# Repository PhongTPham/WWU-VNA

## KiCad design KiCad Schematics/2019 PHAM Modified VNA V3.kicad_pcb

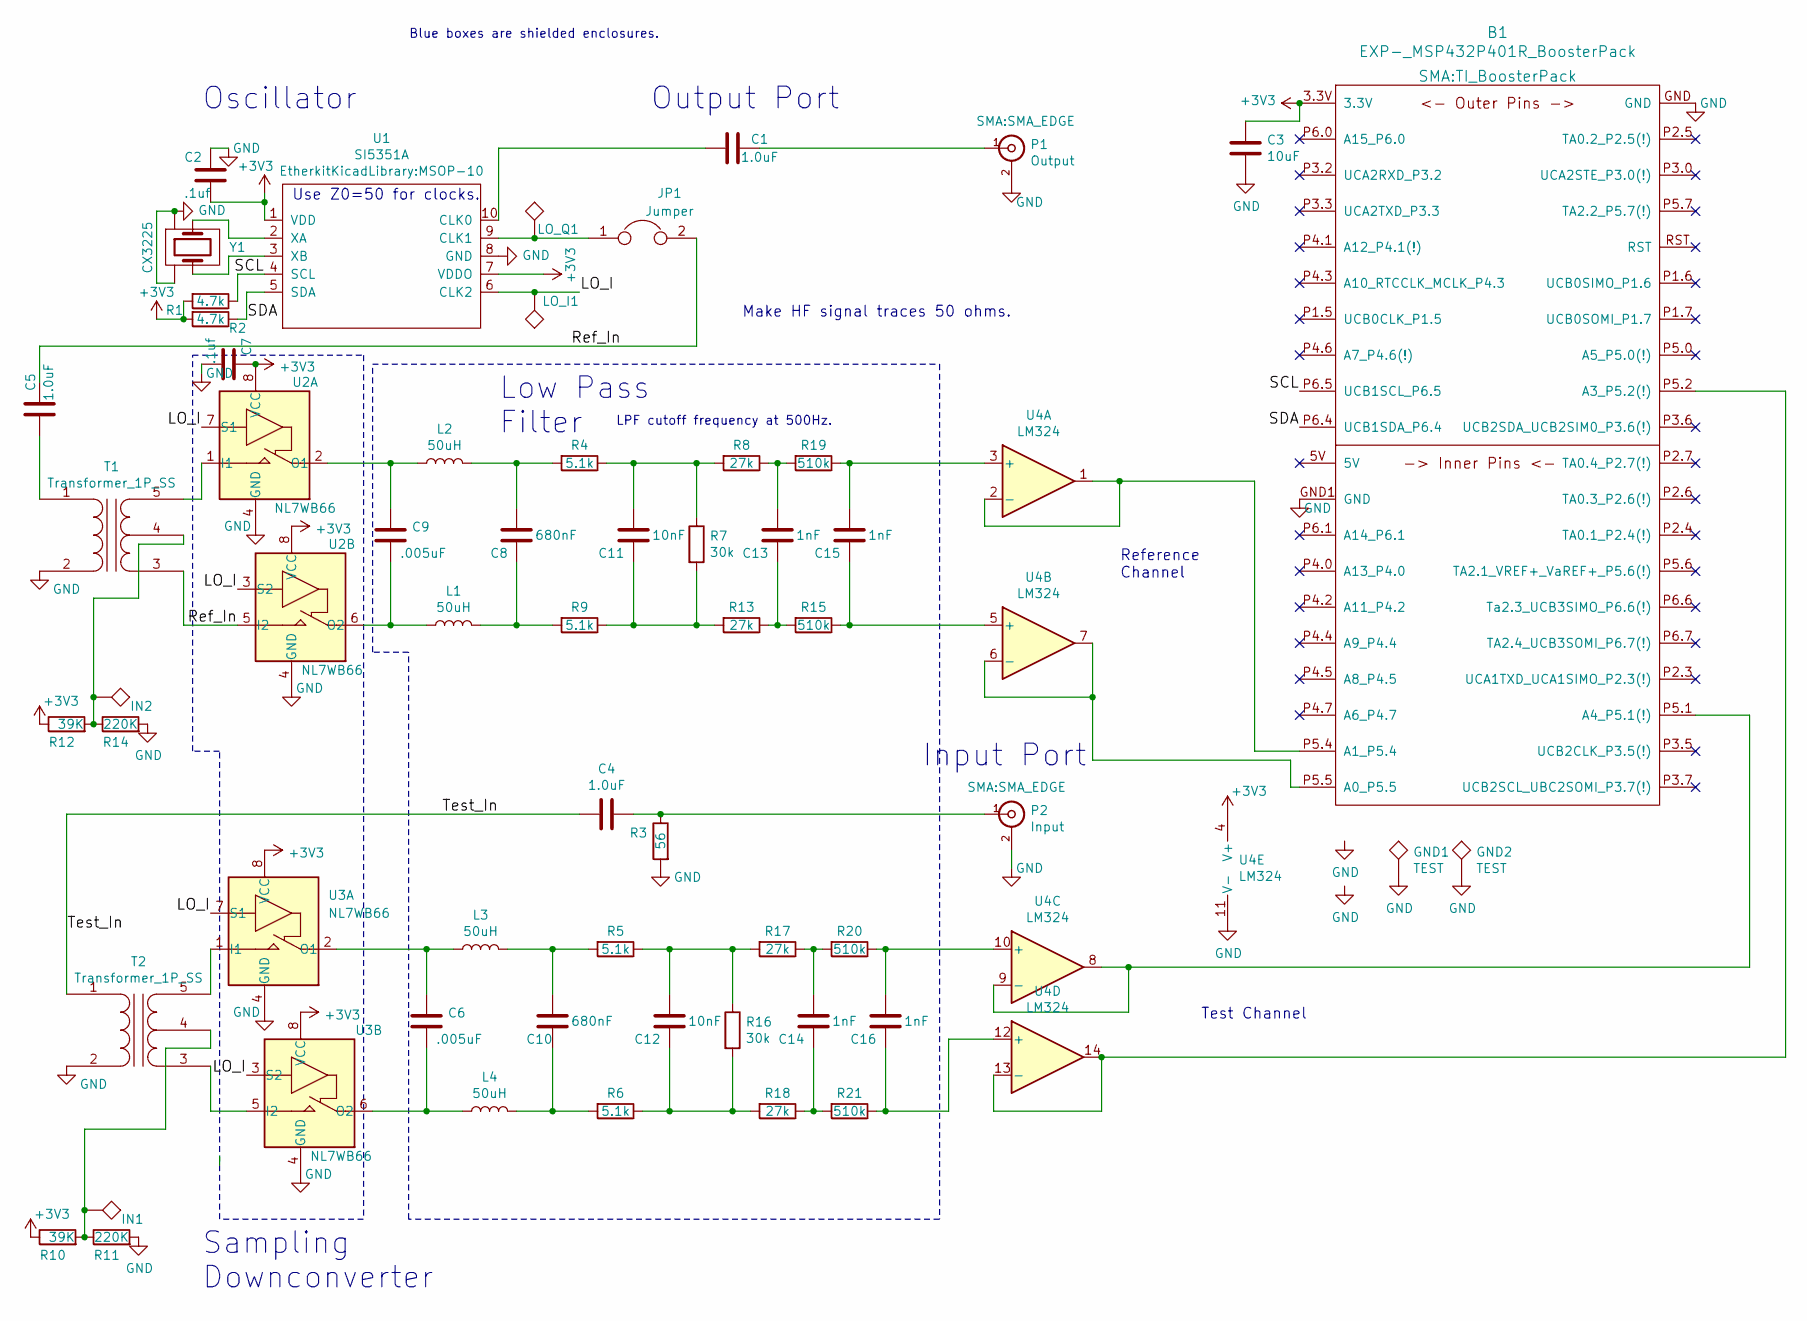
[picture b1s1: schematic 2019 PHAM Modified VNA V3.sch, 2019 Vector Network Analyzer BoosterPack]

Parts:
B1: EXP-_MSP432P401R_BoosterPack; TI_BoosterPack
C1, C4, C5: 1.0uF; C_0805
C2, C7: .1uf; C_0805
C3: 10uF; C_0805
C6, C9: .005uF; C_0805
C8, C10: 680nF; C_0805
C11, C12: 10nF; C_0805
C13, C14, C15, C16: 1nF; C_0805
GND1, GND2: TEST; TestPoint_Keystone_5000-5004_Miniature
IN1, IN2: IN; TestPoint_Keystone_5000-5004_Miniature
JP1: Jumper; SolderJumper-2_P1.3mm_Bridged2Bar_Pad1.0x1.5mm
L1, L2, L3, L4: 50uH; L_0805_2012Metric; Part Taiyo Yuden LB2012T101K
LO_I1: LO_I; TestPoint_Keystone_5000-5004_Miniature
LO_Q1: LO_Q; TestPoint_Keystone_5000-5004_Miniature
P1: Output; SMA_EDGE
P2: Input; SMA_EDGE
R1, R2: 4.7k; R_0805
R3: 56; R_0805
R4, R5, R6, R9: 5.1k; R_0805
R7, R16: 30k; R_0805
R8, R13, R17, R18: 27k; R_0805
R10, R12: 39K; R_0805
R11, R14: 220K; R_0805
R15, R19, R20, R21: 510k; R_0805
T1, T2: Transformer_1P_SS; Pulse_P0926NL
U1: SI5351A; MSOP-10
U2, U3: NL7WB66; VFSOP-8
U4: LM324; SOIC-14_3.9x8.7mm_P1.27mm
Y1: CX3225

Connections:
+3V3: B1.3.3V, C2.2, C3.1, C7.1, R1.2, R2.2, R10.1, R12.1, U1.1 (VDD), U1.7 (VDDO), U2.8 (VCC), U3.8 (VCC), U4.4 (V+)
/LO_I: LO_I1.1, U1.6 (CLK2), U2.3 (S2), U2.7 (S1), U3.3 (S2), U3.7 (S1)
/Ref_In: C5.1, JP1.2, T1.3 (SA), U2.5 (I2)
/SCL: B1.P6.5 (UCB1SCL_P6.5), R1.1, U1.4 (SCL)
/SDA: B1.P6.4 (UCB1SDA_P6.4), R2.1, U1.5 (SDA)
/Test_In: C4.1, T2.1 (AA)
GND: B1.GND, B1.GND1 (GND), C2.1, C3.2, C7.2, GND1.1, GND2.1, P1.2 (Ext), P2.2 (Ext), R3.2, R11.2, R14.2, T1.2 (AB), T2.2 (AB), U1.8 (GND), U2.4 (GND), U3.4 (GND), U4.11 (V-), Y1.2 (GND), Y1.4 (GND)
unnamed: B1.P5.1 (A4_P5.1(!)), U4.8, U4.9 (-)
unnamed: B1.P5.2 (A3_P5.2(!)), U4.13 (-), U4.14
unnamed: B1.P5.4 (A1_P5.4), U4.1, U4.2 (-)
unnamed: B1.P5.5 (A0_P5.5), U4.6 (-), U4.7
unnamed: C1.1, P1.1 (In)
unnamed: C1.2, U1.10 (CLK0)
unnamed: C4.2, P2.1 (In), R3.1
unnamed: C5.2, T1.1 (AA)
unnamed: C6.1, L3.1, U3.2 (O1)
unnamed: C6.2, L4.1, U3.6 (O2)
unnamed: C8.1, L2.2, R4.2
unnamed: C8.2, L1.2, R9.2
unnamed: C9.1, L2.1, U2.2 (O1)
unnamed: C9.2, L1.1, U2.6 (O2)
unnamed: C10.1, L3.2, R5.2
unnamed: C10.2, L4.2, R6.2
unnamed: C11.1, R4.1, R7.1, R8.2
unnamed: C11.2, R7.2, R9.1, R13.2
unnamed: C12.1, R5.1, R16.1, R17.2
unnamed: C12.2, R6.1, R16.2, R18.2
unnamed: C13.1, R8.1, R19.2
unnamed: C13.2, R13.1, R15.2
unnamed: C14.1, R17.1, R20.2
unnamed: C14.2, R18.1, R21.2
unnamed: C15.1, R19.1, U4.3 (+)
unnamed: C15.2, R15.1, U4.5 (+)
unnamed: C16.1, R20.1, U4.10 (+)
unnamed: C16.2, R21.1, U4.12 (+)
unnamed: IN1.1, R10.2, R11.1, T2.4 (SC)
unnamed: IN2.1, R12.2, R14.1, T1.4 (SC)
unnamed: JP1.1, LO_Q1.1, U1.9 (CLK1)
unnamed: T1.5 (SB), U2.1 (I1)
unnamed: T2.3 (SA), U3.5 (I2)
unnamed: T2.5 (SB), U3.1 (I1)
unnamed: U1.2 (XA), Y1.1
unnamed: U1.3 (XB), Y1.3 (2)

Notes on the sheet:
Use Z0=50 for clocks.
Test Channel
Reference Channel
Make HF signal traces 50 ohms.
Output Port
Oscillator
Blue boxes are shielded enclosures.
Low Pass Filter
Sampling Downconverter
LPF cutoff frequency at 500Hz.
Input Port

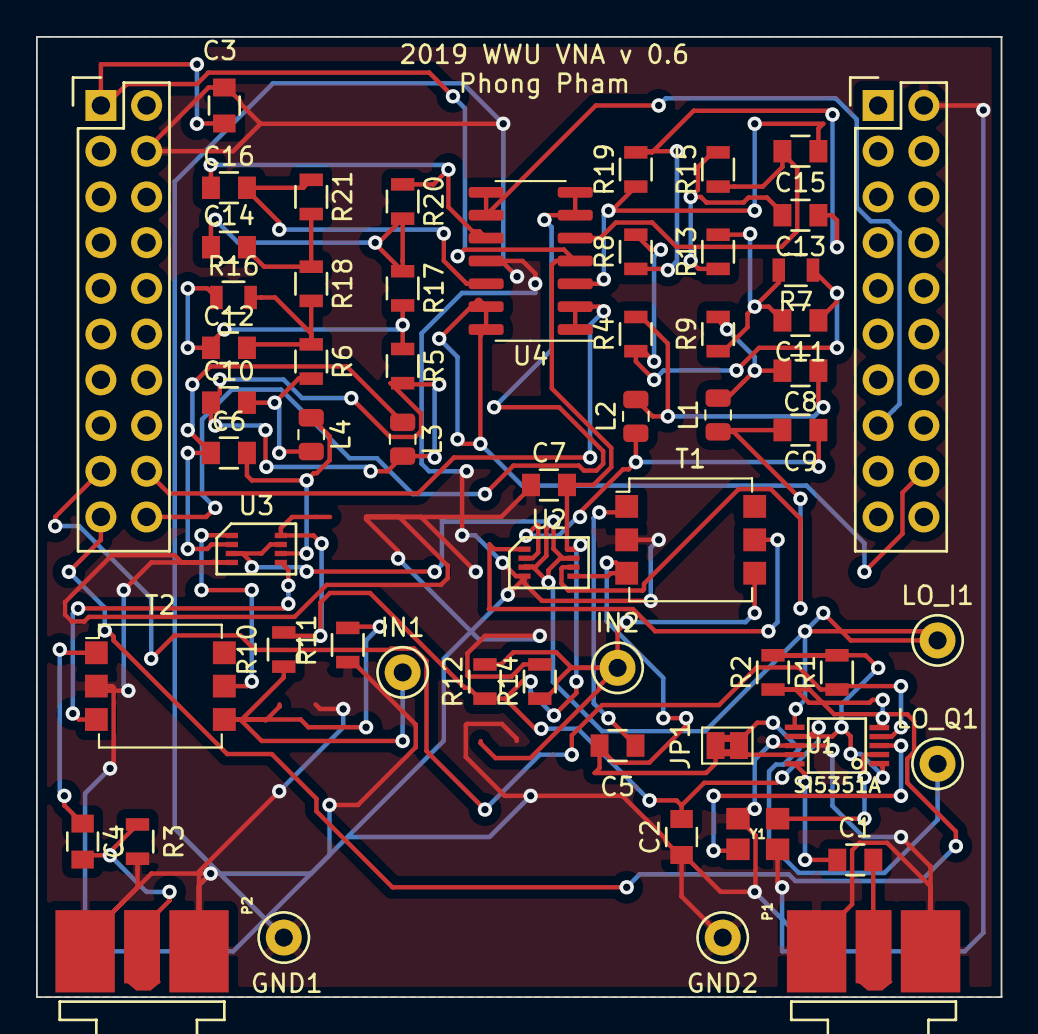
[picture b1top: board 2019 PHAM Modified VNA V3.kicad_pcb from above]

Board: 2 copper layers, 53.6 x 53.3 mm, 58 parts (0 on the bottom side), 43 nets.

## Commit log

2019-06-03 Libraries for the Energia code
    Libraries for ADC14VNA, ADC14singleDifferential2SCompliment, Constants, DCP, Si5351 and Signal Processing
2019-06-03 The Energia code used for the VNA
2019-06-03 KICAD Files for Differential VNA
    PCB, Schematic and BOM for differential VNA
2019-06-12 Create Differential VNA README
2019-06-12 Adding CLK1 to oscillator code
2019-06-12 LTSpice Models
    An LTSpice model with the differential LPFS and transformers. Works as intended
    An LTSpice model with the above and op amps. This one needs work
